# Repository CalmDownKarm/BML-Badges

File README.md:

# BML-Badges
Swag/Activity badges handed out for BML Munjal University

##To Do
*Change circuit to run off single/double 3V button cells for better form factor
*Design Board in Eagle/Ki

Current design made by Skot Weidmann at The University of Illinois

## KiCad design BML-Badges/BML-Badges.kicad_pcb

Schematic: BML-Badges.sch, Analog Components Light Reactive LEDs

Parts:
BT1: 3V
C1, C2, C3: 22uF
D1, D2, D3: LED
PHOTOR1, PHOTOR2, PHOTOR3: PHOTOR
Q1, Q2, Q3: PN2222A; TO92
R1, R3, R5: 50
R2, R4, R6: 100k

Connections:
3V: BT1.1 (+), R1.1, R2.1, R3.1, R4.1, R5.1, R6.1
GND: BT1.2 (-), C1.2, C2.2, C3.2, PHOTOR1.2, PHOTOR2.2, PHOTOR3.2, Q1.1 (E), Q2.1 (E), Q3.1 (E)
unnamed: C1.1, PHOTOR1.1, Q1.2 (B), R2.2
unnamed: D1.2, Q1.3 (C)
unnamed: D1.1, R1.2
unnamed: D2.2, Q2.3 (C)
unnamed: D3.2, Q3.3 (C)
unnamed: C3.1, PHOTOR3.1, Q3.2 (B), R6.2
unnamed: D3.1, R5.2
unnamed: C2.1, PHOTOR2.1, Q2.2 (B), R4.2
unnamed: D2.1, R3.2

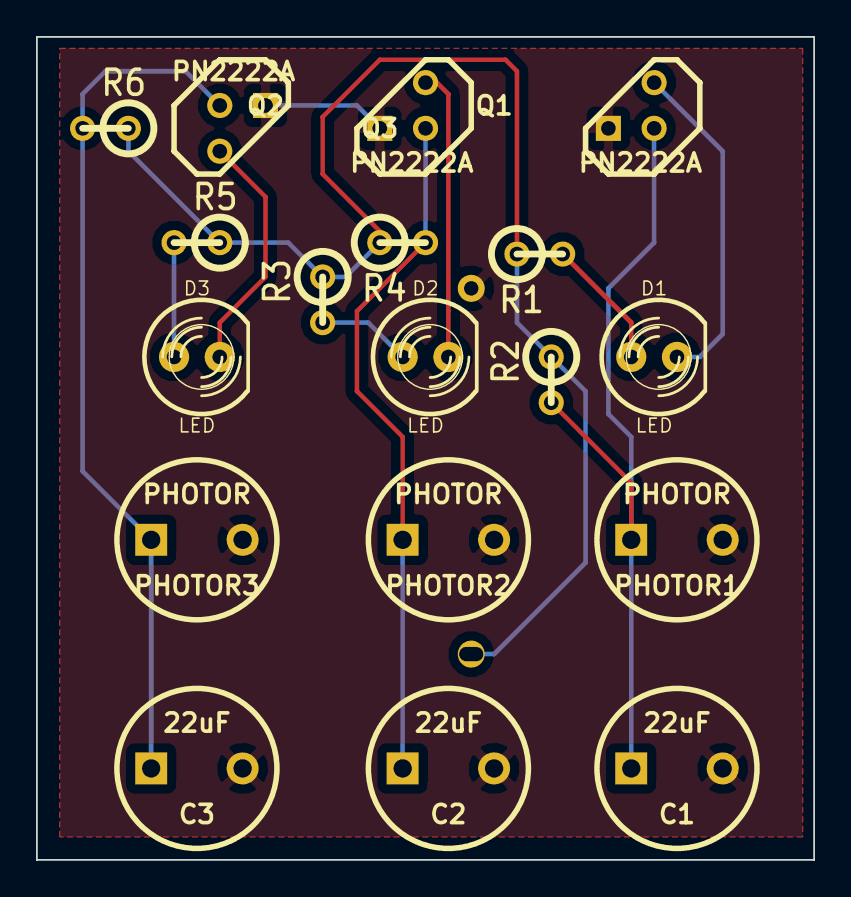
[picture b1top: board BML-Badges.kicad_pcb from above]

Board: 2 copper layers, 43.2 x 45.7 mm, 19 parts (1 on the bottom side), 11 nets.

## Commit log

2015-06-28 added files
2015-08-20 Midway Through
2015-08-20 Naptime
2015-08-21 version1complete
2015-08-21 floating transistors
2015-08-22 Added Anools Contribution
2015-08-22 abcd
